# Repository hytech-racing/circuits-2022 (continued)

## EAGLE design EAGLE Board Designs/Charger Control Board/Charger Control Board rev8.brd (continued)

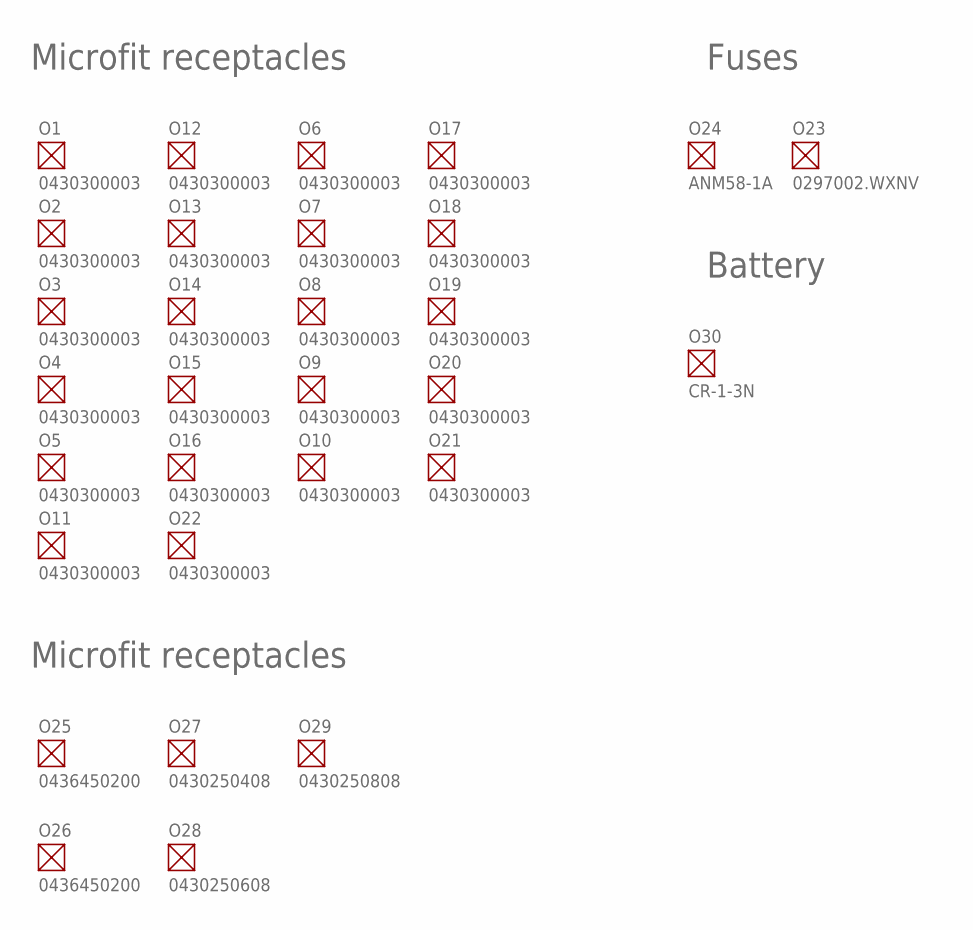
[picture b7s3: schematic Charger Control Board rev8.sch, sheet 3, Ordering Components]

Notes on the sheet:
Microfit receptacles
Fuses
Battery

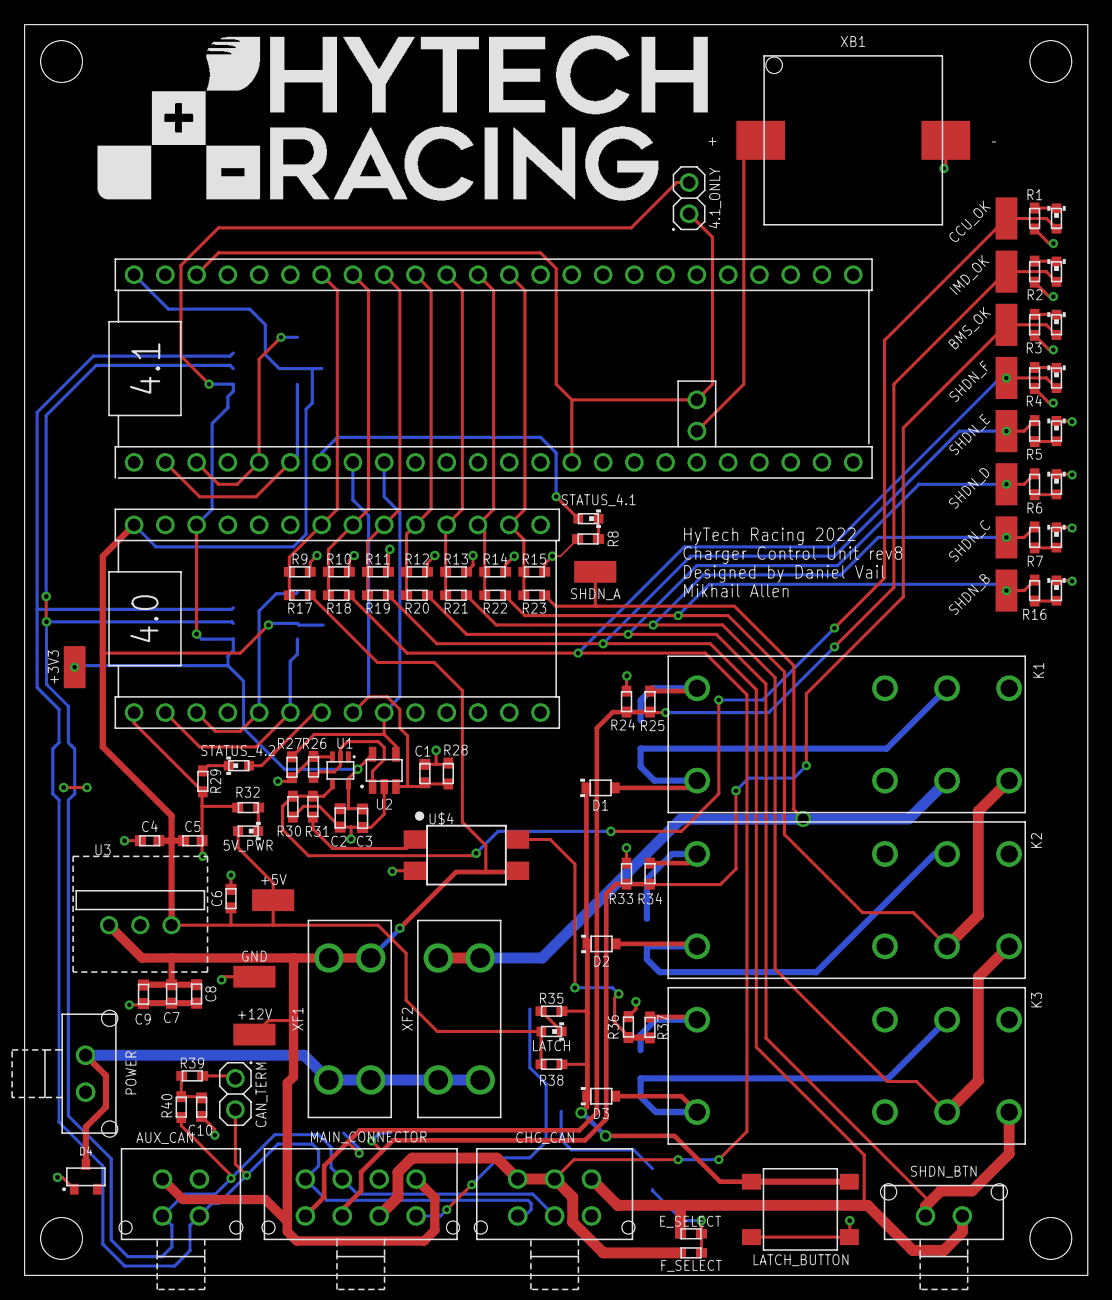
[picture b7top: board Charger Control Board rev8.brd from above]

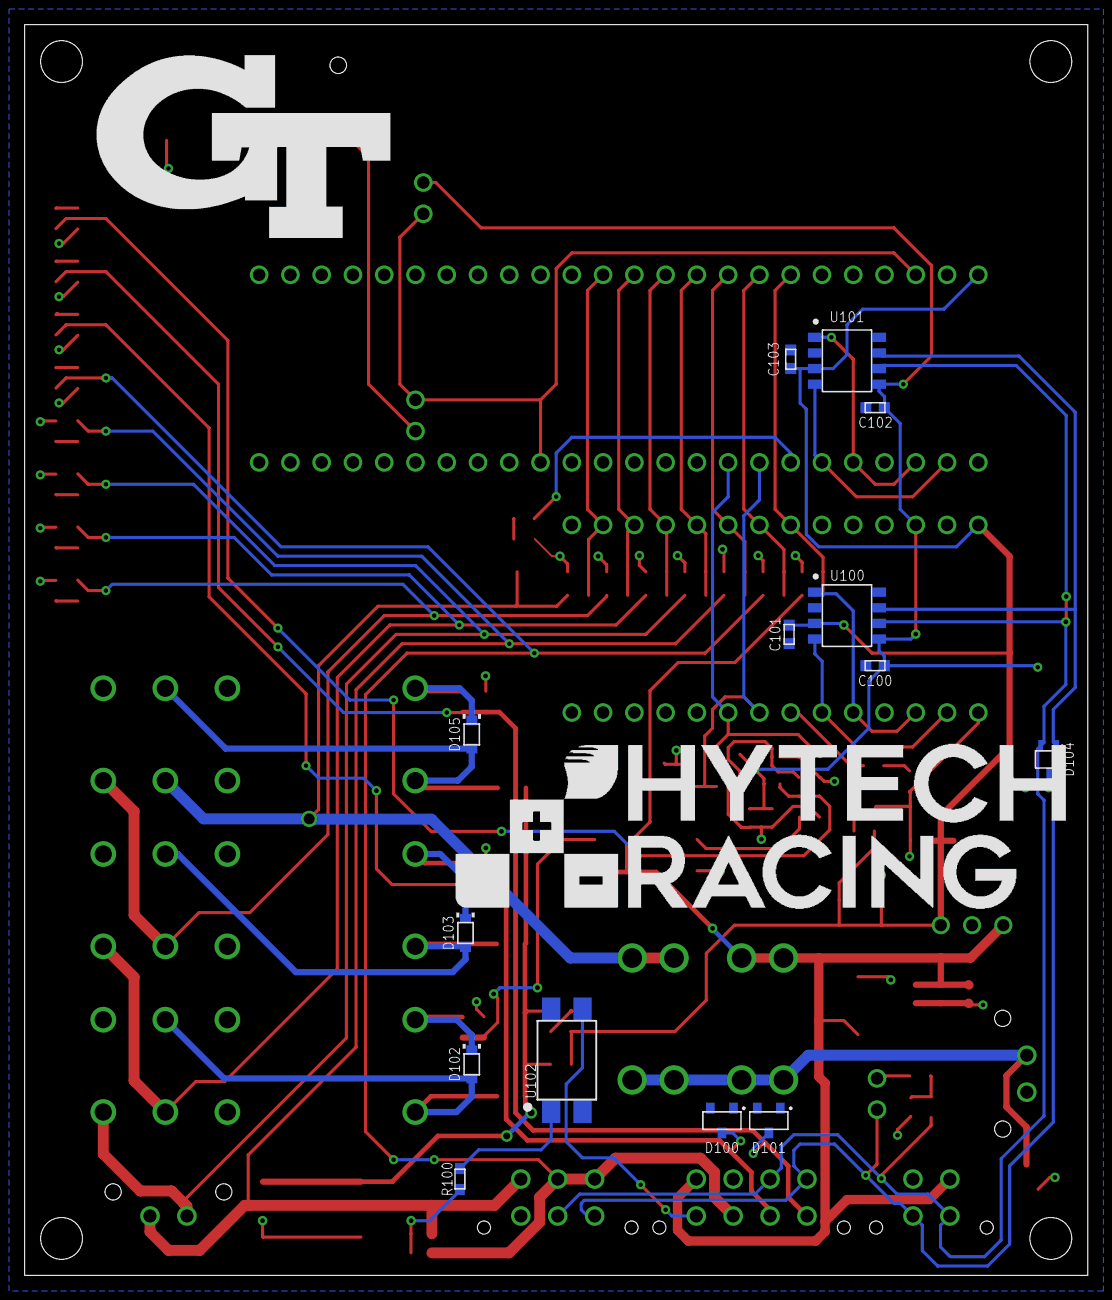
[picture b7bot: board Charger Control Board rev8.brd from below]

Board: 2 copper layers, 86.4 x 101.6 mm, 122 parts (16 on the bottom side), 60 nets.

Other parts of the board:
U$1, U$2, U$5, U$6: MOUNTING_M3
U$3, U$101: LOGO_HYTECH_LARGE
U$102: LOGO_GT_LARGE

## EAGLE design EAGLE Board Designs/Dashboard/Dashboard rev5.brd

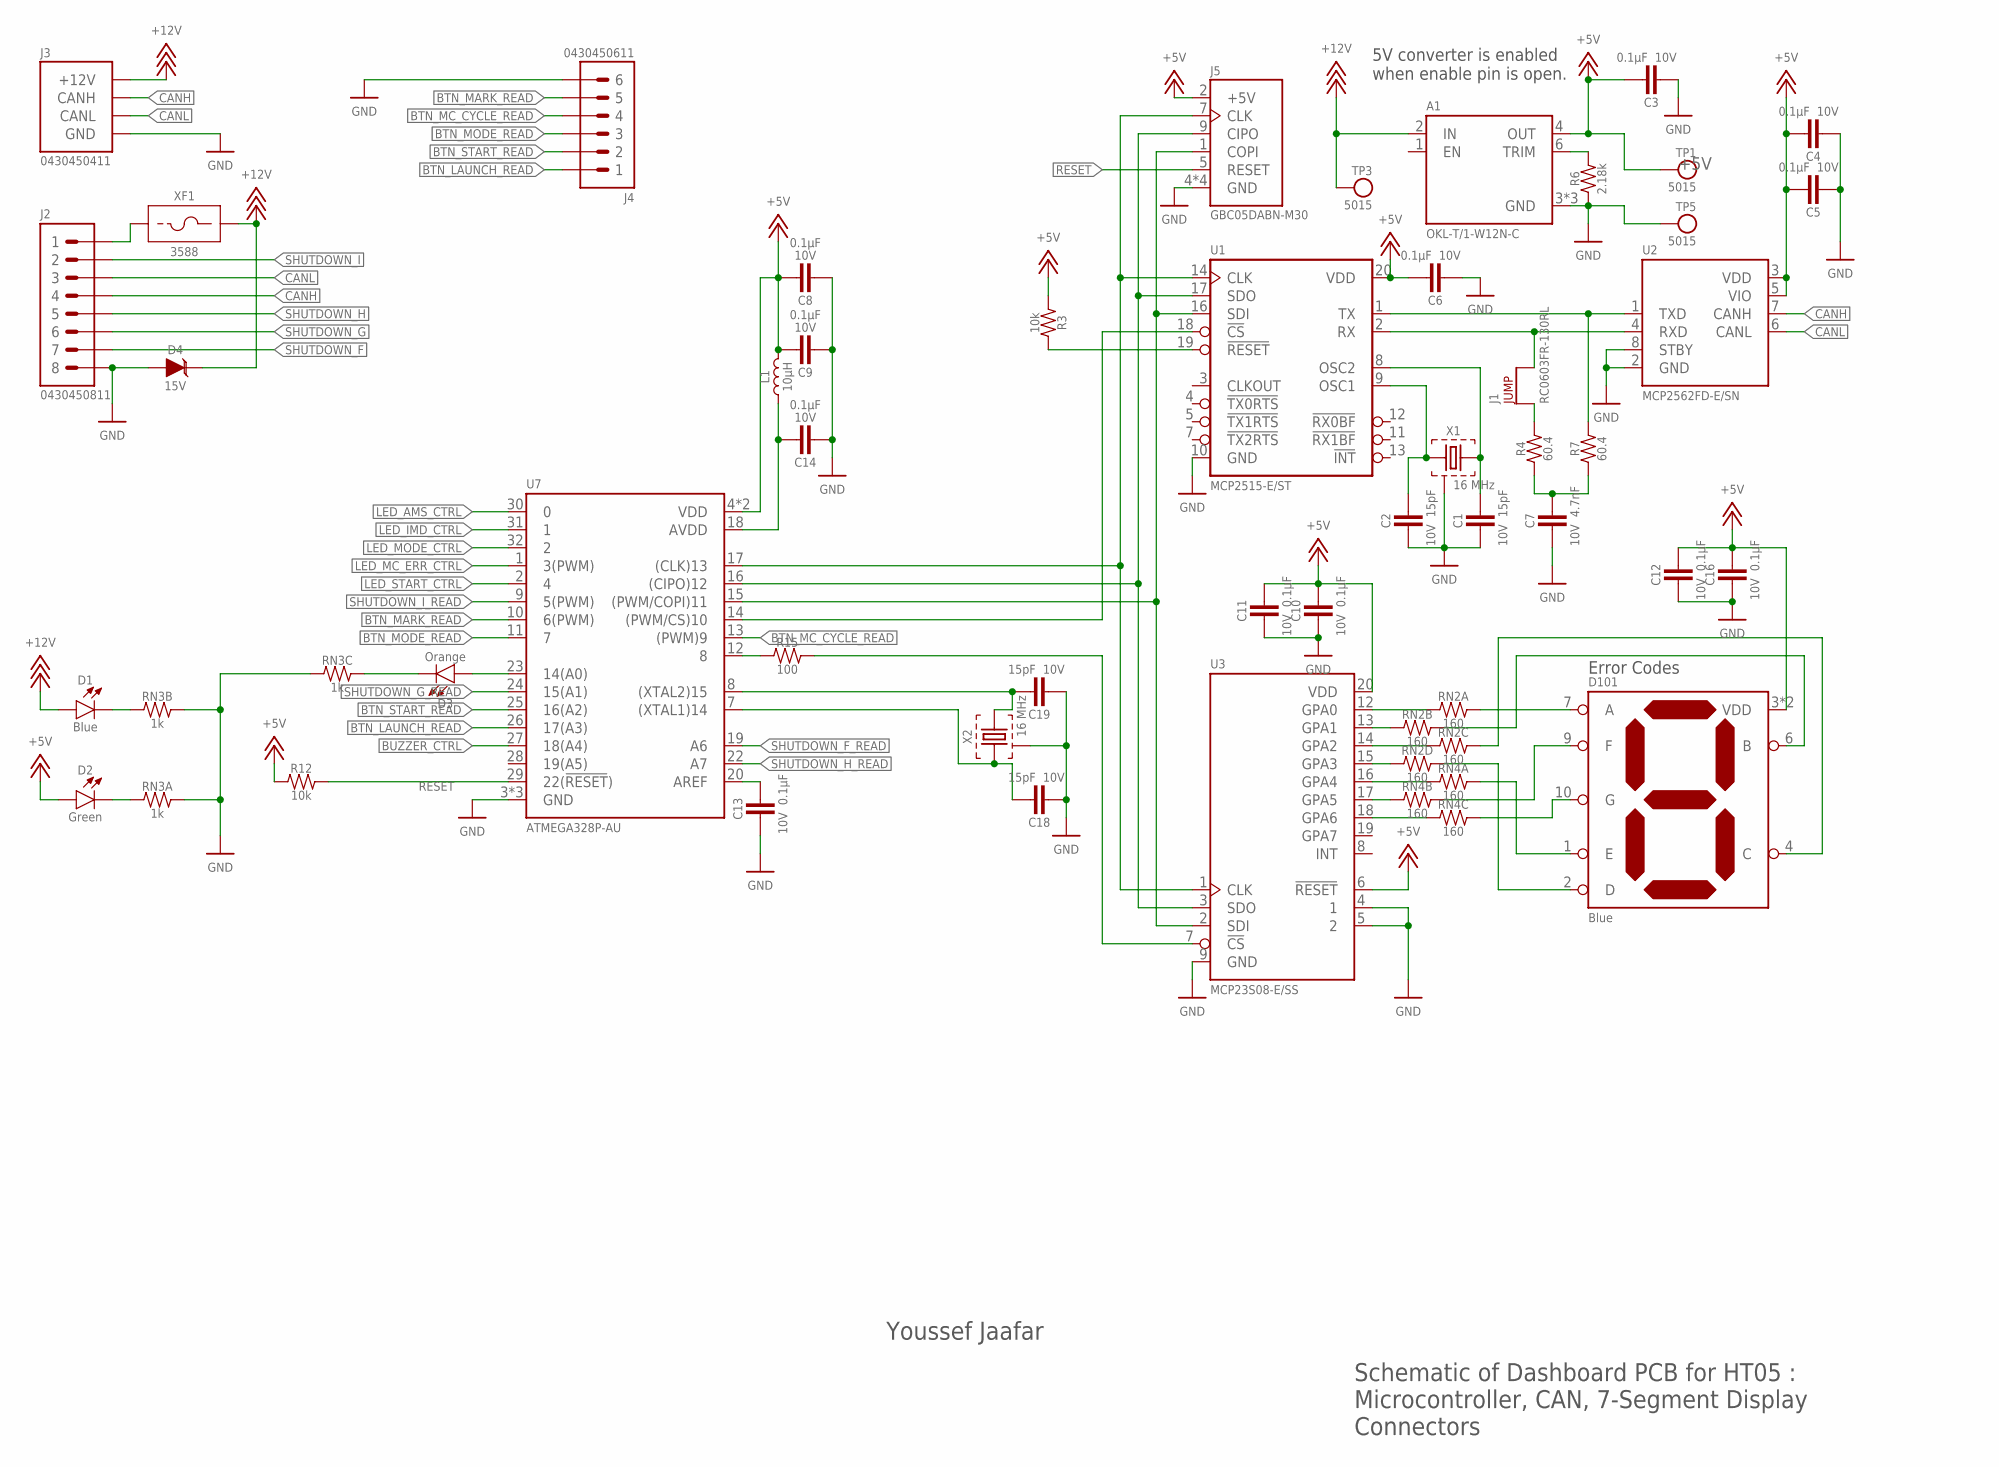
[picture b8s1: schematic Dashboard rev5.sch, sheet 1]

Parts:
A1: OKL-T/1-W12N-COKL; OKL-T/1-W12
C1, C2, C18, C19: CAPACITOR_0603_10V_15PF; 0603-CAP
C3, C4, C5, C6, C8, C9, C10, C11, C12, C13, C14, C16: CAPACITOR_0603_10V_0.1UF; 0603-CAP
C7: CAPACITOR_0603_10V_4.7NF; 0603-CAP
D1: LED_0603_BLUE; 0603-LED
D2: LED_0603_GREEN; 0603-LED
D3: LED_0603_ORANGE; 0603-LED
D4: TVS_15V; SOT-23
D101: LED_7_SEGMENT_BLUE_DSM7TA; DSM7T
J1: JUMPER_0603_; 0603-RES
J2: CONNECTOR-8_μF_S_RA_; MOLEX_MICROFIT_SMD_RIGHTANGLE_08_DUAL
J3: CONNECTOR-CAN_μF_S_RA_; MOLEX_MICROFIT_SMD_RIGHTANGLE_04_DUAL
J4: CONNECTOR-6_μF_S_RA_; MOLEX_MICROFIT_SMD_RIGHTANGLE_06_DUAL
J5: CONNECTOR-AVR-ISP_2X05_SMD; 2X05_SMD
L1: INDUCTOR_LQM18DH100M70_10UH; 0603-IND
R3, R12: RESISTOR_0603_10K; 0603-RES
R4, R7: RESISTOR_0603_60.4; 0603-RES
R6: RESISTOR_0603_2.18K; 0603-RES
R15: RESISTOR_0603_100; 0603-RES
RN2, RN4: RESISTOR_NETWORK_4_160; 1206-RES-ARRAY
RN3: RESISTOR_NETWORK_4_1K; 1206-RES-ARRAY
TP1, TP3, TP5: TEST_POINT; 5015
U1: MCP2515; TSSOP-20
U2: MCP2562FD; SOIC-08(NARROW,0.15")
U3: MCP23S08; SSOP-20
U7: ATMEGA328P-AU; TQFP-32
X1, X2: CRYSTAL_16MHZ; ECX-42
XF1: FUSE_HOLDER_MINIBLADESMD; 3588

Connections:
+5V: A1.4 (OUT), C3.1, C4.1, C5.1, C6.1, C8.1, C9.1, C10.1, C11.1, C12.1, C16.1, D2.2 (A), D101.3 (VDD), D101.8 (VDD), J5.2 (+5V), L1.2, R3.1, R12.1, TP1.1, U1.20 (VDD), U2.3 (VDD), U2.5 (VIO), U3.6 (!RESET), U3.20 (VDD), U7.4 (VDD), U7.6 (VDD); also elsewhere on the board
+12V: A1.2 (IN), D1.2 (A), D4.3 (C), J3.1 (+12V), TP3.1, XF1.3 (2), XF1.4 (2); also elsewhere on the board
A2: RN2.1, U3.12 (GPA0)
B2: RN2.2 (1), U3.13 (GPA1)
BTN_LAUNCH_READ: J4.1, U7.26 (17(A3))
BTN_MARK_READ: J4.5, U7.10 (6(PWM))
BTN_MC_CYCLE_READ: J4.4, U7.13 ((PWM)9)
BTN_MODE_READ: J4.3, U7.11 (7)
BTN_START_READ: J4.2, U7.25 (16(A2))
BUZZER_CTRL: U7.27 (18(A4)); also elsewhere on the board
C2: RN2.3 (1), U3.14 (GPA2)
CANH: J2.4, J3.4 (CANH), U2.7 (CANH)
CANL: J2.3, J3.3 (CANL), U2.6 (CANL)
CIPO: J5.9 (CIPO), U1.17 (SDO), U3.3 (SDO), U7.16 ((CIPO)12)
CLK: J5.7 (CLK), U1.14 (CLK), U3.1 (CLK), U7.17 ((CLK)13)
COPI: J5.1 (COPI), U1.16 (SDI), U3.2 (SDI), U7.15 ((PWM/COPI)11)
CS_CAN: U1.18 (!CS), U7.14 ((PWM/CS)10)
CS_IO: R15.2, U3.7 (!CS)
D2: RN2.4 (1), U3.15 (GPA3)
E2: RN4.1, U3.16 (GPA4)
F2: RN4.2 (1), U3.17 (GPA5)
G2: RN4.3 (1), U3.18 (GPA6)
GND: A1.3 (GND), A1.7 (GND), A1.11 (GND), C1.2, C2.2, C3.2, C4.2, C5.2, C6.2, C7.2, C8.2, C9.2, C10.2, C11.2, C12.2, C13.2, C14.2, C16.2, C18.2, C19.2, D4.1 (A), J2.8, J3.2 (GND), J4.6, J5.4 (GND), J5.6 (GND), J5.8 (GND), J5.10 (GND), R6.1, RN3.3 (1), RN3.7 (2), RN3.8 (2), TP5.1, U1.10 (GND), U2.2 (GND), U2.8 (STBY), U3.4 (1), U3.5 (2), U3.9 (GND), U7.3 (GND), U7.5 (GND), U7.21 (GND), X1.2 (GND), X1.4 (GND), X2.2 (GND), X2.4 (GND); also elsewhere on the board
LED_AMS_CTRL: U7.30 (0); also elsewhere on the board
LED_IMD_CTRL: U7.31 (1); also elsewhere on the board
LED_MC_ERR_CTRL: U7.1 (3(PWM)); also elsewhere on the board
LED_MODE_CTRL: U7.32 (2); also elsewhere on the board
LED_START_CTRL: U7.2 (4); also elsewhere on the board
unnamed: C2.1, U1.9 (OSC1), X1.1
unnamed: C19.1, U7.8 ((XTAL2)15), X2.3
unnamed: C13.1, U7.20 (AREF)
unnamed: C18.1, U7.7 ((XTAL1)14), X2.1
unnamed: D101.7 (A), RN2.8 (2)
unnamed: D101.6 (B), RN2.7 (2)
unnamed: D101.4 (C), RN2.6 (2)
unnamed: D101.10 (G), RN4.6 (2)
unnamed: D101.9 (F), RN4.7 (2)
unnamed: D101.1 (E), RN4.8 (2)
unnamed: D101.2 (D), RN2.5 (2)
unnamed: D2.1 (C), RN3.1
unnamed: R15.1, U7.12 (8)
unnamed: A1.6 (TRIM), R6.2
unnamed: J1.2, U1.2 (RX), U2.4 (RXD)
unnamed: C1.1, U1.8 (OSC2), X1.3
unnamed: J2.1, XF1.1, XF1.2 (1)
unnamed: D3.2 (A), U7.23 (14(A0))
unnamed: R3.2, U1.19 (!RESET)
unnamed: J1.1, R4.2
unnamed: C7.1, R4.1, R7.1
unnamed: R7.2, U1.1 (TX), U2.1 (TXD)
unnamed: C14.1, L1.1, U7.18 (AVDD)
RESET: J5.5 (RESET), R12.2, U7.29 (22(!RESET!))
SHUTDOWN_F: J2.7; also elsewhere on the board
SHUTDOWN_F_READ: U7.19 (A6); also elsewhere on the board
SHUTDOWN_G: J2.6; also elsewhere on the board
SHUTDOWN_G_READ: U7.24 (15(A1)); also elsewhere on the board
SHUTDOWN_H: J2.5; also elsewhere on the board
SHUTDOWN_H_READ: U7.22 (A7); also elsewhere on the board
SHUTDOWN_I: J2.2; also elsewhere on the board
SHUTDOWN_I_READ: U7.9 (5(PWM)); also elsewhere on the board
STATUS_12V: D1.1 (C), RN3.2 (1)
STATUS_TEENSY: D3.1 (C), RN3.6 (2)

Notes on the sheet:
Youssef Jaafar
Schematic of Dashboard PCB for HT05 : Microcontroller, CAN, 7-Segment Display Connectors
Error Codes
5V converter is enabled when enable pin is open.

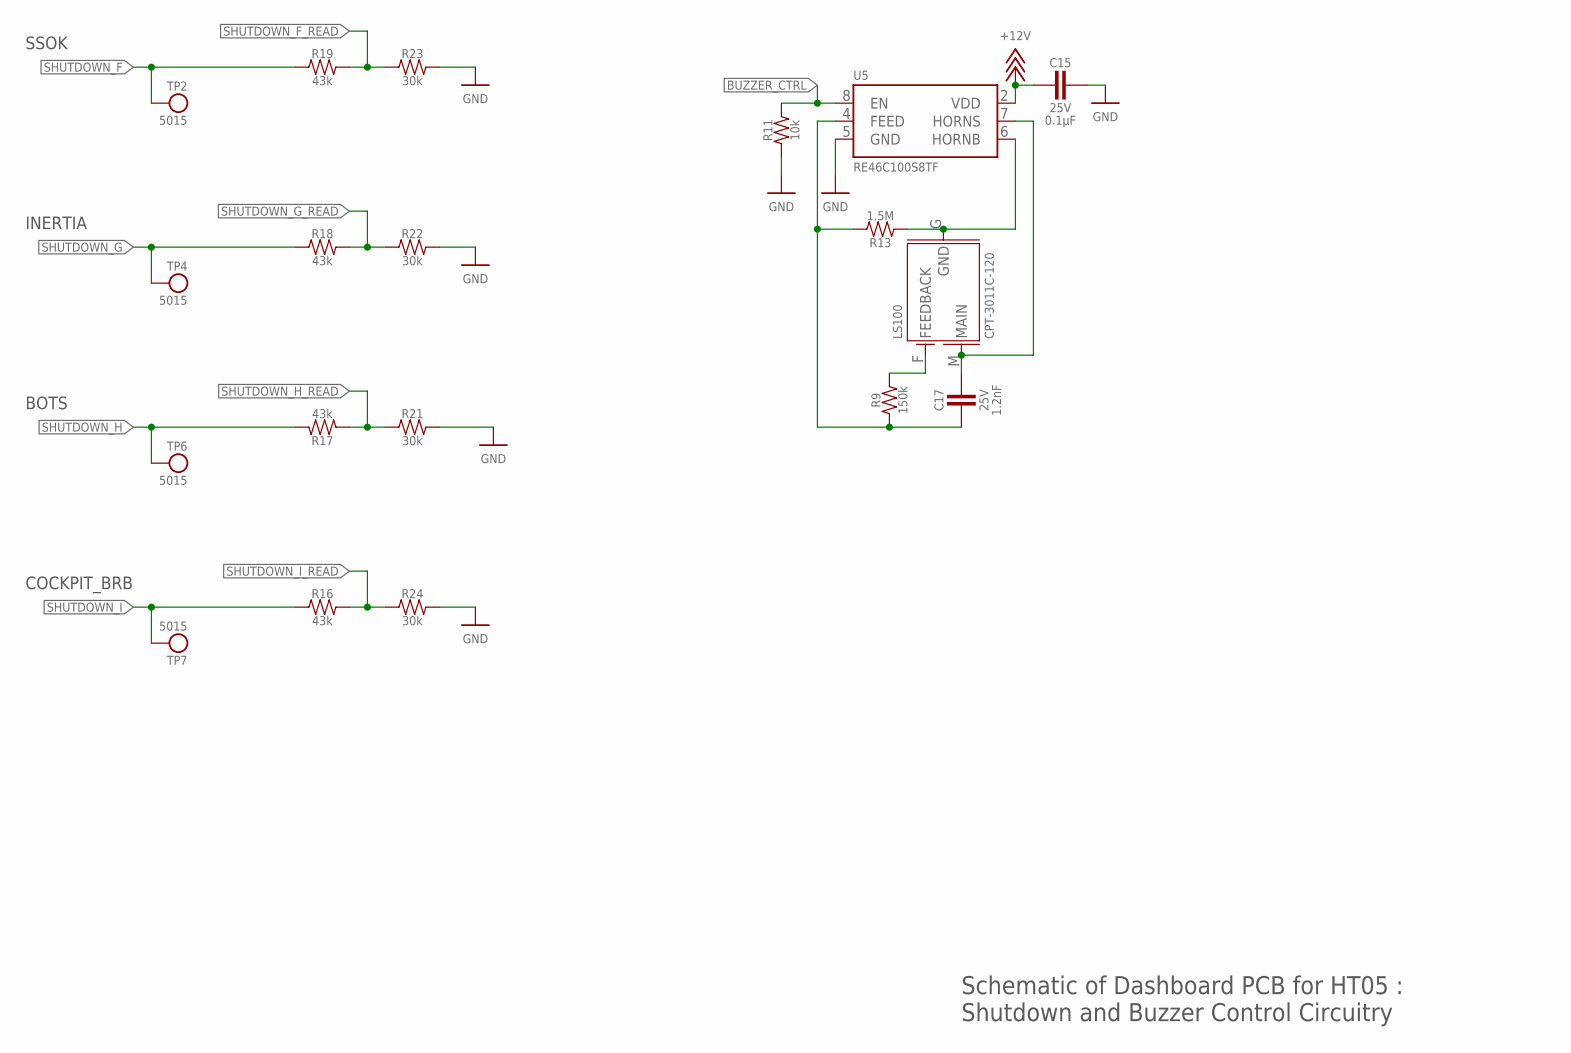
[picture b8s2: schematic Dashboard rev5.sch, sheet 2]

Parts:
C15: CAPACITOR_0603_25V_0.1UF; 0603-CAP
C17: CAPACITOR_0603_25V_1.2NF; 0603-CAP
LS100: BUZZER_3_PIN_CPT-3011C-120; CPT-3011C-120
R9: RESISTOR_0603_150K; 0603-RES
R11: RESISTOR_0603_10K; 0603-RES
R13: RESISTOR_0603_1.5M; 0603-RES
R16, R17, R18, R19: RESISTOR_0603_43K; 0603-RES
R21, R22, R23, R24: RESISTOR_0603_30K; 0603-RES
TP2, TP4, TP6, TP7: TEST_POINT; 5015
U5: RE46C100; SOIC-08(NARROW,0.15")

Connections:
+12V: C15.2, U5.2 (VDD); also elsewhere on the board
BUZZER_CTRL: R11.2, U5.8 (EN); also elsewhere on the board
GND: C15.1, R11.1, R21.2, R22.2, R23.2, R24.2, U5.5 (GND); also elsewhere on the board
unnamed: C17.1, LS100.M (MAIN), U5.7 (HORNS)
unnamed: LS100.G (GND), R13.1, U5.6 (HORNB)
unnamed: C17.2, R9.1, R13.2, U5.4 (FEED)
unnamed: LS100.F (FEEDBACK), R9.2
SHUTDOWN_F: R19.1, TP2.1; also elsewhere on the board
SHUTDOWN_F_READ: R19.2, R23.1; also elsewhere on the board
SHUTDOWN_G: R18.1, TP4.1; also elsewhere on the board
SHUTDOWN_G_READ: R18.2, R22.1; also elsewhere on the board
SHUTDOWN_H: R17.1, TP6.1; also elsewhere on the board
SHUTDOWN_H_READ: R17.2, R21.1; also elsewhere on the board
SHUTDOWN_I: R16.1, TP7.1; also elsewhere on the board
SHUTDOWN_I_READ: R16.2, R24.1; also elsewhere on the board

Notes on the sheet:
SSOK
INERTIA
Schematic of Dashboard PCB for HT05 : Shutdown and Buzzer Control Circuitry
COCKPIT_BRB
BOTS

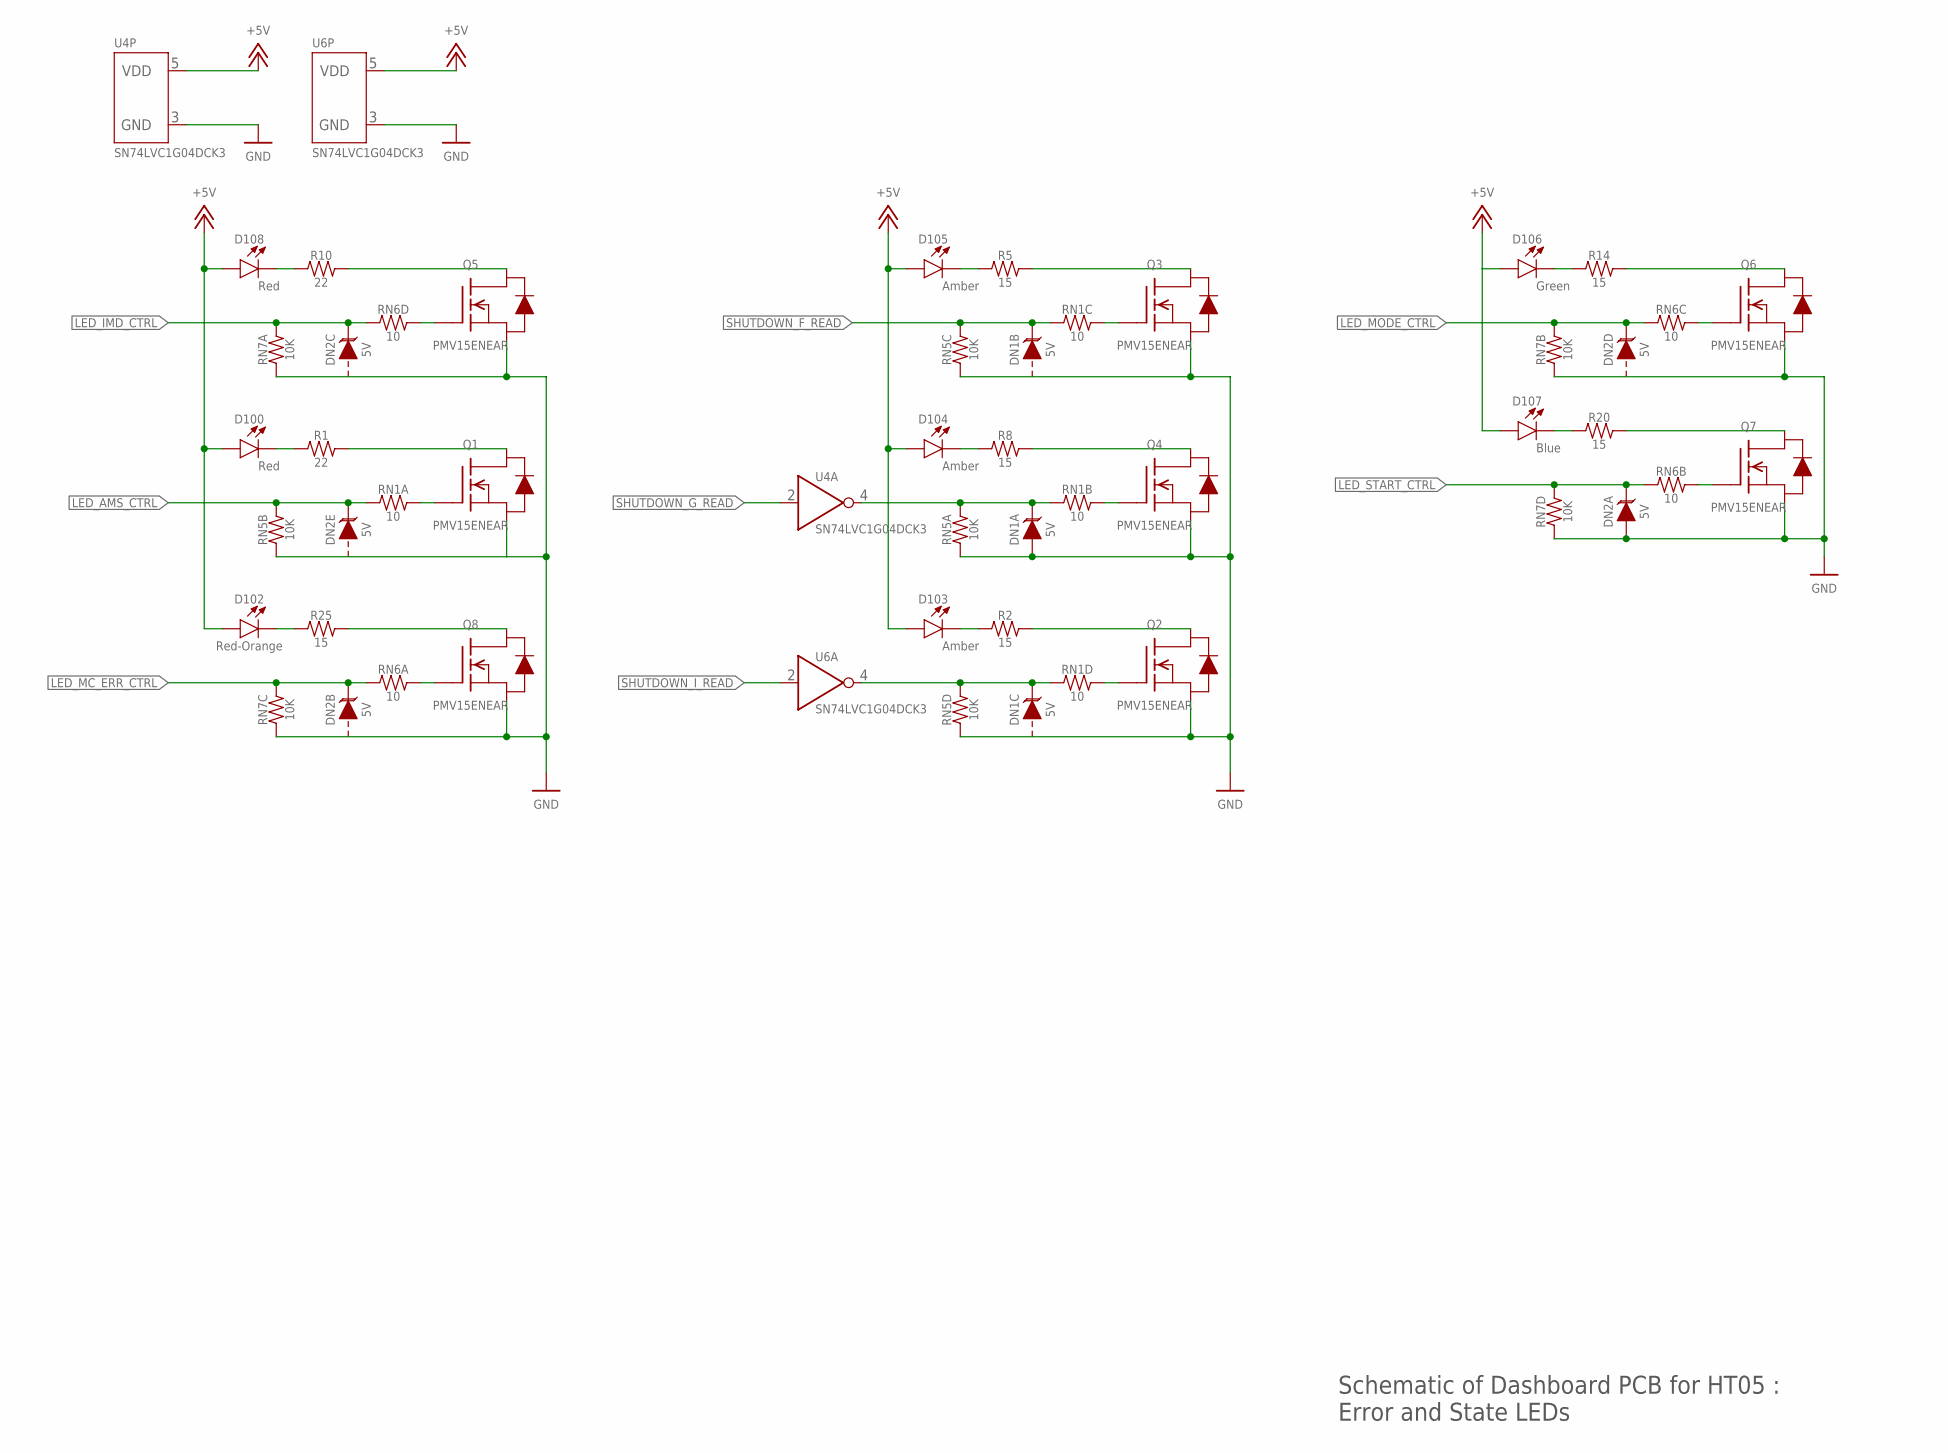
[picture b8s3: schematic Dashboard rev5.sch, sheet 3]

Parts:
D100, D108: LED_2835_RED; 2835-LED
D102: LED_2835_RED-ORANGE; 2835-LED
D103, D104, D105: LED_2835_AMBER; 2835-LED
D106: LED_2835_GREEN; 2835-LED
D107: LED_2835_BLUE; 2835-LED
DN1, DN2: TVS_ARRAY_5V; SOT-363
Q1, Q2, Q3, Q4, Q5, Q6, Q7, Q8: TRANSISTOR_N_MOS__PMV15ENEA; SOT-23
R1, R10: RESISTOR_0805_22; 0805-RES
R2, R5, R8, R14, R20, R25: RESISTOR_0603_15; 0603-RES
RN1, RN6: RESISTOR_NETWORK_4_10; 1206-RES-ARRAY
RN5, RN7: RESISTOR_NETWORK_4_10K; 1206-RES-ARRAY
U4, U6: LOGICGATE_INVERTER_DCK3; SC-70-5

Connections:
+5V: D100.A, D102.A, D103.A, D104.A, D105.A, D106.A, D107.A, D108.A, U4.5 (VDD), U6.5 (VDD); also elsewhere on the board
AMS_LED-: D100.C, R1.1
BRB_LED-: D103.C, R2.1
GND: DN1.2 (A), DN2.2 (A), Q1.2 (S), Q2.2 (S), Q3.2 (S), Q4.2 (S), Q5.2 (S), Q6.2 (S), Q7.2 (S), Q8.2 (S), RN5.1, RN5.2 (1), RN5.3 (1), RN5.4 (1), RN7.1, RN7.2 (1), RN7.3 (1), RN7.4 (1), U4.3 (GND), U6.3 (GND); also elsewhere on the board
IMD_LED-: D108.C, R10.1
LED_AMS_CTRL: DN2.6 (C), RN1.1, RN5.7 (2); also elsewhere on the board
LED_IMD_CTRL: DN2.4 (C), RN6.4 (1), RN7.8 (2); also elsewhere on the board
LED_MC_ERR_CTRL: DN2.3 (C), RN6.1, RN7.6 (2); also elsewhere on the board
LED_MODE_CTRL: DN2.5 (C), RN6.3 (1), RN7.7 (2); also elsewhere on the board
LED_START_CTRL: DN2.1 (C), RN6.2 (1), RN7.5 (2); also elsewhere on the board
MCU_LED-: D102.C, R25.1
MODE_LED-: D106.C, R14.1
unnamed: Q8.3 (D), R25.2
unnamed: Q6.3 (D), R14.2
unnamed: Q5.3 (D), R10.2
unnamed: Q1.3 (D), R1.2
unnamed: Q4.3 (D), R8.2
unnamed: Q7.1 (G), RN6.7 (2)
unnamed: Q2.1 (G), RN1.5 (2)
unnamed: Q8.1 (G), RN6.8 (2)
unnamed: Q2.3 (D), R2.2
unnamed: Q3.1 (G), RN1.6 (2)
unnamed: Q7.3 (D), R20.2
unnamed: Q5.1 (G), RN6.5 (2)
unnamed: Q6.1 (G), RN6.6 (2)
unnamed: Q4.1 (G), RN1.7 (2)
unnamed: Q1.1 (G), RN1.8 (2)
unnamed: DN1.1 (C), RN1.2 (1), RN5.8 (2), U4.4 (!IN)
unnamed: Q3.3 (D), R5.2
unnamed: DN1.4 (C), RN1.4 (1), RN5.5 (2), U6.4 (!IN)
S/D_F_LED-: D105.C, R5.1
S/D_G_LED-: D104.C, R8.1
SHUTDOWN_F_READ: DN1.3 (C), RN1.3 (1), RN5.6 (2); also elsewhere on the board
SHUTDOWN_G_READ: U4.2 (IN); also elsewhere on the board
SHUTDOWN_I_READ: U6.2 (IN); also elsewhere on the board
START_LED-: D107.C, R20.1

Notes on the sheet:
Schematic of Dashboard PCB for HT05 : Error and State LEDs

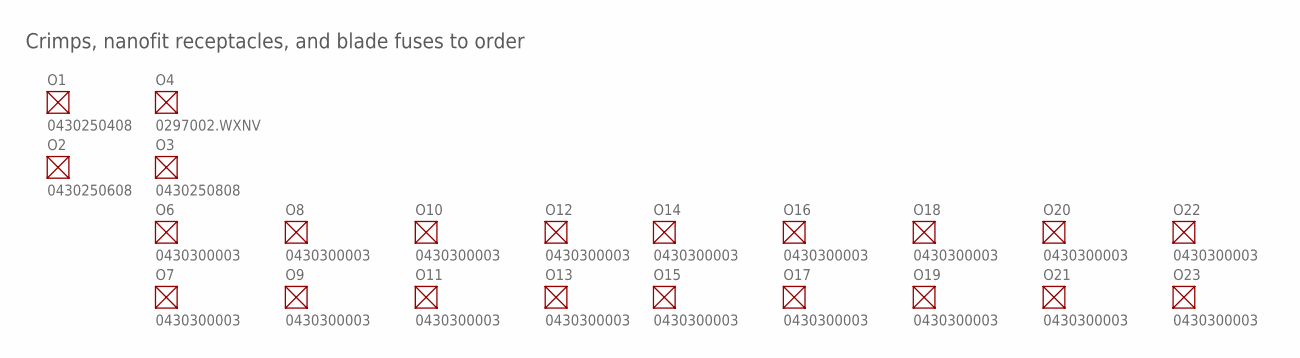
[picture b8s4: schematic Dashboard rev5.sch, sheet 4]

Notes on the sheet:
Crimps, nanofit receptacles, and blade fuses to order

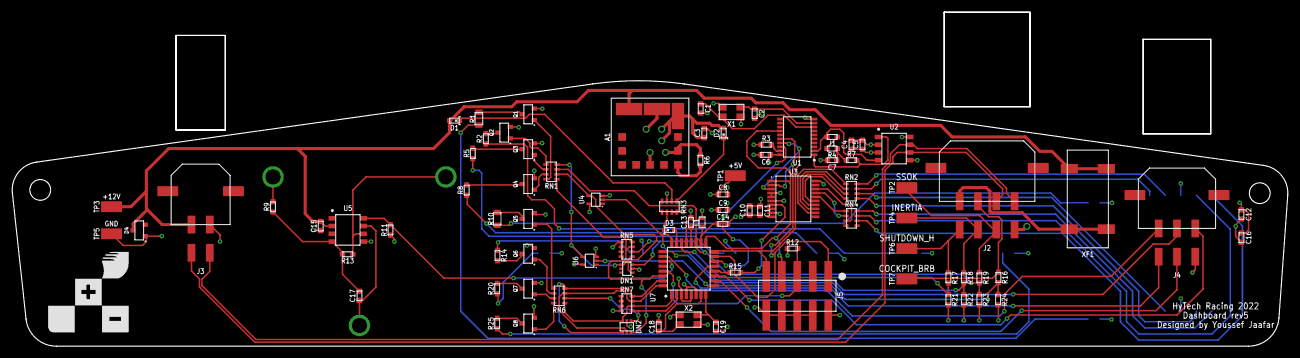
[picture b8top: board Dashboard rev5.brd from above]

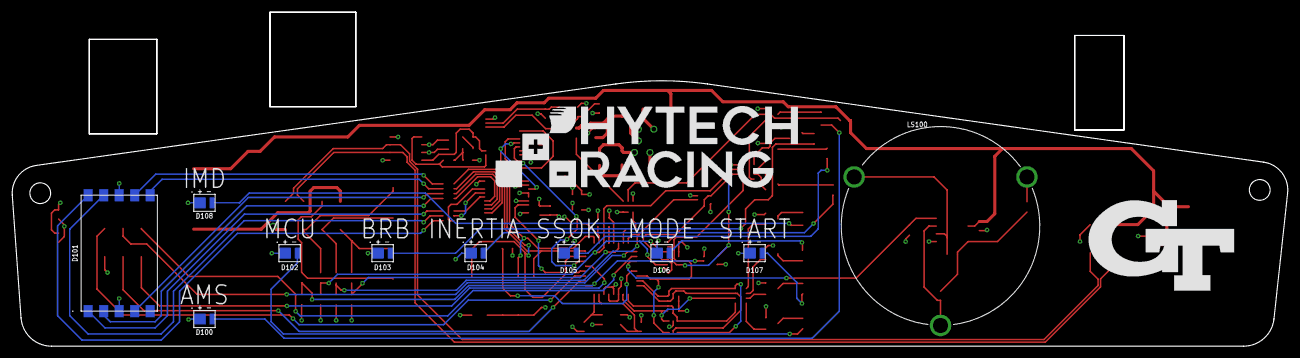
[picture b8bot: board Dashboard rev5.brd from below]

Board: 4 copper layers, 209.1 x 43.5 mm, 104 parts (12 on the bottom side), 92 nets.

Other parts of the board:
U$1, U$2: MOUNTING_M3
U$3: LOGO_HYTECH_SQUARE_EXTRA_LARGE
U$100: LOGO_GT_LARGE
U$101: LOGO_HYTECH_LARGE

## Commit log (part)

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2021-12-25 Fixed schematic (updated) and routing according to desired changes
2021-12-26 Added testpoints, descriptions, and labels
2021-12-26 Replaced GLVB OV/UV Resistors
2021-12-26 updated ked symbol, added frame
2021-12-27 Cleaning up
2021-12-27 Updated name
2021-12-27 Changed top silkscreen
2021-12-27 Updated connectors
2021-12-27 Weird error with last commit. Redid Cody's changes.
2021-12-27 Deleted arbitrary relay input
2021-12-27 updated led symbol
2021-12-27 Swapped diodes, updated parts, minor changes
2021-12-27 Board fixes
2021-12-28 Improved documentation for AMS rev17 design
2021-12-28 Documentation changes
2021-12-28 Minor fixes and adding additonal parts sheet
2021-12-28 Created Board, added thermal net to schematic
2021-12-28 Made some changes listed in changelog
2021-12-28 updated resistors, right angle connector
2021-12-29 Ams rev 17 (#25)
    * Created new board, laid out springs, started laying out components
    * Fixed ERC errors
    * holder push
    * Revert "holder push"
    This reverts commit 5c5a8d45b60ff0506a7db83585d04c86d1c2f773.
    * more preliminary board layout
2021-12-29 Cleanup
2021-12-29 Updated to new 4421 symbol. Reorganized.
2021-12-29 Resolved merge conflicts
2021-12-29 Prepped rev 18 with updated lib
2021-12-29 updated library
2021-12-29 Added new sense resistors, other changes
2021-12-29 Replaced OV/UV resistors
2021-12-29 Finishing touches
2021-12-29 Fixed xml issue
2021-12-29 Updated testpoints
2021-12-29 Replaced fuses with fuse holders
2021-12-29 fully compliant with DRC
2021-12-29 crimps, logo
2021-12-29 Renumbered and fixed CAN routing
2021-12-30 Switched to Lumiled 2835 series LEDs
2021-12-30 brd and schem finalized
2021-12-30 Fixed test points
2021-12-30 Fixed silkscreen clownery
2021-12-30 corrected nanofits to microfits; order files
2021-12-31 Finalizing setup
2021-12-31 Fast startup times
2022-01-01 Replaced with jumpers
2022-01-02 some changes in response to ESF comments
2022-01-02 updated from library; silkscreen now incorrect
2022-01-02 moved connector to bottom layer
2022-01-02 Revert "fixed + - symbols"
    This reverts commit 69f4a8db28469720d14382a6a82e278377962e57.
2022-01-02 fixed +-, put connector on bottom
2022-01-02 updated led silkscreen
2022-01-03 centered connector
2022-01-03 Looks good fixing silkscreen
2022-01-04 added signature for board review
2022-01-05 Tractive system active light rev4 (#29)
    * TSAL rev4
    * tsal rev4
    changed led symbol, added frame, changed to common power
    * Update Tractive System Active Light rev4.sch
    * Update Tractive System Active Light rev4.sch
    * updated ked symbol, added frame
2022-01-05 Dashboard rev3 (#30)
    * Copied Dashboard rev3 files from dashboard rev2
    * incomplete changes to schamatic for rev3 features
    * Updated names to wires
    * Minor deletions because of the sensor board
    * Just working on rev3
    * Dashboard rev3
2022-01-05 update 8v tvs diode to have correct pn
2022-01-06 edited LED and mounting hole positions, added DXF
2022-01-07 More board work
2022-01-09 update board for on campus drc
2022-01-10 Tsal mech electrical reconciliation (#31)
    * edited LED and mounting hole positions, added DXF
    * order files
2022-01-10 fix ACU rev1 schematic
2022-01-10 Moved board dimensions
2022-01-10 Moved connector to point down
2022-01-10 extended thermal planes
2022-01-10 Redid board layout/routing
2022-01-12 changed name
2022-01-12 added fuses
2022-01-13 updated isoSPI circuit and routed new board
2022-01-13 More board revisions
2022-01-13 Minor board edit
2022-01-14 Made the major schematic and board design changes needed for the last rev
2022-01-15 Made final changes to schematic
2022-01-16 routed fuses
2022-01-16 aligned stuff
2022-01-16 more changes to rev2
2022-01-16 Minor fixes
2022-01-16 Final minor changes
2022-01-17 Fixed fonts
2022-01-17 changed voltage dividers
2022-01-17 added missing resistors
2022-01-17 tvs diodes
2022-01-17 added silkscreen
2022-01-17 Made final board changes
2022-01-18 Fixed molex connectors
2022-01-18 Updates following board review
    - Renumbered
    - Resistor divider values changed
    - Added extra tvs protection
    - Swapped watchdog
    - Fixed LED colors
    - Added RPC control relay, jumpers for triggering off of SHDN E and F
2022-01-19 Made necessary changes to begin new board design
2022-01-19 Replaced some items in schematic
2022-01-19 Made schematic changes
2022-01-19 Deleted previous board file (to restart)
2022-01-19 Fixed fuse value
2022-01-19 New board part 1
2022-01-19 Updated ordered info
2022-01-19 Board changes part 3
2022-01-19 Esf rev2 (#32)
    * all but TSAL updated
    * some changes in response to ESF comments
    * updated all schem to comply with ESF comments
    * esf updates completed
    * added missing resistors
2022-01-20 fixed fuses and silk screen
2022-01-20 More silkscreen fixes
2022-01-20 Moving logo
2022-01-20 Fixed ordering components for microfit connectors
2022-01-20 Placing files to begin front/rear boards
2022-01-20 finished board
2022-01-20 fixed fuse silkscreens
2022-01-20 Created sch for front rev 1
2022-01-20 Tractive system active light rev5 (#34)
    * Moved parts on board
    * Moved board dimensions
    * Moved connector to point down
    * move mounting holes 50 mils higher
    * extended thermal planes
    * order files
2022-01-20 Added notes for wrong isoSPI
2022-01-20 Charger controller rev 7 (#35)
    * Initial Revision 7
    Changed to teensy 4.0, removed efuse and charger control relay, added new connector for charger
    * New rev7 schematic
    Made new rev7 schematic using updated component library (work in progress)
    * Complete rev7 schematic
    Finished making rev7 schematic using new eagle parts library
2022-01-20 minor cleanup
2022-01-20 Removing files that should be in sharepoint
2022-01-20 4 board to panelize
2022-01-20 Fixing naming
2022-01-20 Board changes part 4
2022-01-20 Board changes part 5
2022-01-21 Board changes part 6
2022-01-21 Replaced components in schematic with ones in library
2022-01-21 More board changes. x1000 on OV/UV resistors
2022-01-21 Fixed testpoints
2022-01-21 Replaced some parts
2022-01-21 Revert "Merge branch 'Power-Switching-Board' of https://github.com/hytech-racing/circuits-2022 into Power-Switching-Board"
    This reverts commit 210c54b0a775197197f1ab2d964e17f32e0beb28, reversing
    changes made to 688ffccce3643ed0dbe36dff112f4bf9f7718e42.
2022-01-21 Revert "Revert "Replaced some parts""
    This reverts commit 177906525b430feff981215040b5890684fe2959.
2022-01-21 Replaced resistors
2022-01-21 Revert "Revert "Merge branch 'Power-Switching-Board' of https://github.com/hytech-racing/circuits-2022 into Power-Switching-Board""
    This reverts commit 26bc2d3ef6be355bfab7107a4d9909b87e7a50e6.
2022-01-21 Renumbered parts. Added TVS diodes.
2022-01-21 Changed LED colors
2022-01-22 Fixed silkscreen
2022-01-22 Minor schematic and board edits
2022-01-22 Updated schematic with modified 680uF cap
2022-01-22 Moved file to PSB folder in EAGLE Board Designs
2022-01-22 some changes
2022-01-22 restored rev7 files
2022-01-22 final changes and order files
2022-01-22 split panel into two
2022-01-22 Created front board
2022-01-22 Fixed schematic stuff. Ran board renumber ULP.
2022-01-22 More silkscreen edits
2022-01-22 Made better next rev
2022-01-22 connect Ultimate GPS to SAB Front Teensy
2022-01-23 Panel (#36)
    * minor cleanup
    * Fixes
    * removing more files that should be in sharepoint
    * 4 board to panelize
    * Fixing naming
    * Delete EAGLE Board Designs/Accumulator Management System/AMS Segment/Order files directory
2022-01-23 Minor board edits. Fixed frame attributes.
2022-01-23 Replaced J2 with new connector in library
2022-01-23 Fixed front
2022-01-23 Fixed GPS connections
2022-01-24 Deletions?
2022-01-24 Changed Rear sensor numbering
2022-01-25 order files (#40)
2022-01-27 corrected Nanofits to Microfits and order files
2022-01-29 Replaced SAB Rear 4.0 with 3.2
2022-02-04 more rear diagram
2022-02-04 Filled in BoM with soldering done
2022-02-04 Revert "Filled in BoM with soldering done"
    This reverts commit 27c52e2b264f9a9b8f8579a309dffad885b99b22.
2022-02-06 add glvms to psb
2022-02-11 SSOK and Inertia Read signals connected to LED nMos switches
2022-02-11 Added inertia and ssok led circuitry, flipped LED, and rerouted
2022-02-11 Removed shutdown circuitry diodes
2022-02-13 Created PSB rev4 files
2022-02-18 Sensor acquisition board front/rear rev1 (#41)
    * Added new folders for front and rear boards, removed deprecated rev1 and rev2
    * Placing files to begin front/rear boards
    * Created sch for front rev 1
    * Started on rear board sch
    * Created Rear board
    * TCAN to MCP on rear
2022-02-18 regrounded with groundplane
2022-02-25 Rerouted dash leds after reorientation
2022-02-25 Changed silkscreen lettering
2022-02-25 Added red-orange led for mcu led
2022-02-25 fix text
2022-02-26 made changes to board design
2022-02-27 More final changes
2022-02-27 Made specified changes to the tsb
2022-02-28 passed review
2022-02-28 Final fixes
2022-02-28 Updated libraries
2022-03-01 revised schematics to reflect most accurate information
2022-03-02 Revert "Some fixes"
    This reverts commit 12d1257df97418106eafc9ff778c5bcc0629b467.
2022-03-02 finished can tester board
2022-03-03 initial rev8
    expanded board. relocated battery for better SD access. replaced linear regulator with switching regulator. relocated test pads and status LEDs. relocated 4.1_only header to not block USB port. reloc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
2022-03-04 Again
2022-03-04 Created correct rev4 files
2022-03-06 made changes to board
2022-03-09 enlarged logo. minor cleaning up.
2022-03-09 routing cleanup
2022-03-10 Added not gates and tractive LED
2022-03-10 Began rewiring
2022-03-10 Working on reconnection
2022-03-11 Schematic changes
    - Fixed r100 value
    - Added latch led pulldown
    - Changed 2 pin connectors to horizontal
    - Removed second software shdn led
2022-03-11 Fixed routing with horizontal 2 pin connectors
2022-03-12 Finished cleaning up traces and labeling some nets
2022-03-15 Switched R100 to 1k, added input filtering to 5v regulator
2022-03-15 "Updated labeling"
2022-03-16 Fixed missing BOM part numbers
2022-03-16 some more changes
2022-03-16 Fixed some routing
2022-03-18 Moved changes to new rev
2022-03-21 Dashboard rev 4 (#45)
    * Added TPs for all shutdown signals
    * SSOK and Inertia Read signals connected to LED nMos switches
    * Added inertia and ssok led circuitry, flipped LED, and rerouted
    * Renamed Inertia and SSOK
    * Removed shutdown circuitry diodes
    * Cleanup up routing and test points
2022-03-25 corrected label layer
2022-03-29 Removed INTVDD LED
2022-03-30 Board design part 1
2022-03-30 Board design part 2
2022-03-30 Connected Data Out pins to GND
2022-03-31 Final fixes of board
2022-04-04 Created rear sab board
2022-04-13 Fixed labeling and incorrect connections
2022-04-13 Changed silkscreen
2022-04-16 more order files
2022-04-16 Added ordering info
2022-04-17 new ordering files
2022-04-22 accumulator
2022-04-24 Updated accumulator internals
    Need to fix dash connectors, TSAL, TSAL connectors, general symbols update from HyTechTemp
2022-04-26 update per arvind
2022-04-26 Added PSB rev 5
2022-04-28 new tsal
2022-05-02 Fixed issues with order of inputs to SSR
2022-05-03 made final changes
2022-05-07 Acu rev 3 (#48)
    * can jumper + moved some footprints
    * can jumper, tsal fuse
    * fix text
    * some changes based on checklist
    * passed review
    * Some fixes
2022-06-11 added descriptions
2022-06-22 clean up file structure
2022-06-22 files cleanup
2022-06-22 Tractive system board rev3 (#42)
    * made changes to board design
    * Finished board design
    * More final changes
    * Made specified changes to the tsb
    * Final chnages
    * Final fixes
2022-06-23 Enerdel adapter rev7 (#43)
    * Create BMS Enerdel Adapter rev7.sch
    * Update BMS Enerdel Adapter rev7.sch
    * Finished rev 7 schematic
    * Update BMS Enerdel Adapter rev7.sch
    * Schematic Framework Finished
    * Update BMS Enerdel Adapter rev7.brd
2022-06-23 Esf rev 3 (#50)
    * revised schematics to reflect most accurate information
    * added wire gauge key
2022-06-23 Tsal rev6 (#51)
    * new tsal
    * order files
2022-06-23 ordering files (#53)
